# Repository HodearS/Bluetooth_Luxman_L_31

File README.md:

### 🇫🇷 Version Française
                    
# Luxman L-31 - Module Bluetooth & DAC Interne

Ce dépôt contient les fichiers de conception matérielle d'une carte d'extension Bluetooth conçue spécifiquement pour s'intégrer à l'intérieur d'un amplificateur intégré Luxman L-31.

L'objectif est d'ajouter une connectivité sans fil moderne (aptX-HD) sans dénaturer l'esthétique d'origine de l'appareil ni altérer la qualité de son chemin analogique.

## Architecture technique

La carte s'alimente directement sur le rail de puissance interne de l'amplificateur (environ 40V DC). Le basculement du signal audio est géré par un relais de signal pour garantir que les entrées analogiques d'origine restent totalement isolées lorsque le module est inactif.

Points clés de la conception :
* **Alimentation :** Utilisation d'un régulateur abaisseur (Buck) acceptant jusqu'à 65V en entrée pour tolérer les variations du rail d'alimentation du Luxman.
* **CEM et Bruit :** Le convertisseur Buck fonctionne en mode "Forced PWM" (fréquence fixe de 400 kHz) afin de repousser le bruit de découpage hors de la bande audible. Le routage sur 4 couches inclut des plans de masse dédiés, du via stitching et des zones d'exclusion RF strictes autour de l'antenne.
* **Chemin audio :** Les composants passifs traitant le signal analogique en sortie de DAC utilisent des condensateurs à diélectrique C0G/NP0 et des résistances à couche mince (thin film) pour éviter l'introduction de distorsions harmoniques.

## Spécifications matérielles

* **Logiciel CAO :** KiCad 10
* **PCB :** 4 couches
* **Régulateur 5V :** Texas Instruments LMR51606XFDBVR
* **LDO 3.3V :** Texas Instruments TPS7A2033PDBVR (avec décharge active)
* **DAC :** ESS Technology ES9023P
* **Module Bluetooth :** Feasycom FSC-BT1026E (sortie I2S/PCM)
* **Relais Audio :** Omron G6K-2F-Y DC3

## Structure du dépôt

Ce dépôt héberge uniquement les fichiers sources du projet KiCad (`.kicad_pro`, `.kicad_sch`, `.kicad_pcb` et BOM). Les fichiers de fabrication (Gerbers, fichiers de placement CPL) ne sont pas versionnés.

## Avertissement de sécurité

L'installation de ce module implique d'intervenir à l'intérieur d'un amplificateur relié au secteur et de manipuler des tensions continues de puissance. Ces modifications s'adressent à des personnes ayant les compétences requises en électronique. Toute modification est effectuée à vos propres risques.

### 🇬🇧 English Version

# Luxman L-31 - Internal Bluetooth & DAC Module

This repository contains the hardware design files for a Bluetooth extension board specifically designed to be integrated inside a Luxman L-31 integrated amplifier.

The goal is to add modern wireless connectivity (aptX-HD) without altering the original aesthetics of the device or degrading its analog signal path.

## Technical Architecture

The board is powered directly from the amplifier's internal power rail (approx. 40V DC). Audio signal switching is handled by a signal relay to ensure the original analog inputs remain completely isolated when the module is inactive.

Key design points:
* **Power Supply:** Use of a step-down (Buck) regulator accepting up to 65V input to tolerate fluctuations in the Luxman's power rail.
* **EMC and Noise:** The Buck converter operates in "Forced PWM" mode (fixed 400 kHz frequency) to push switching noise out of the audible band. The 4-layer routing includes dedicated ground planes, via stitching, and strict RF keep-out zones around the antenna.
* **Audio Path:** Passive components handling the analog signal at the DAC output use C0G/NP0 dielectric capacitors and thin film resistors to prevent the introduction of harmonic distortion.

## Hardware Specifications

* **CAD Software:** KiCad 10
* **PCB:** 4 layers
* **5V Regulator:** Texas Instruments LMR51606XFDBVR
* **3.3V LDO:** Texas Instruments TPS7A2033PDBVR (with active discharge)
* **DAC:** ESS Technology ES9023P
* **Bluetooth Module:** Feasycom FSC-BT1026E (I2S/PCM output)
* **Audio Relay:** Omron G6K-2F-Y DC3

## Repository Structure

This repository hosts only the KiCad project source files (`.kicad_pro`, `.kicad_sch`, `.kicad_pcb` and BOM). Manufacturing files (Gerbers, CPL placement files) are not versioned.

## Safety Warning

Installing this module involves working inside a mains-connected amplifier and handling high-power DC voltages. These modifications are intended for individuals with the required electronics skills. All modifications are performed at your own risk.

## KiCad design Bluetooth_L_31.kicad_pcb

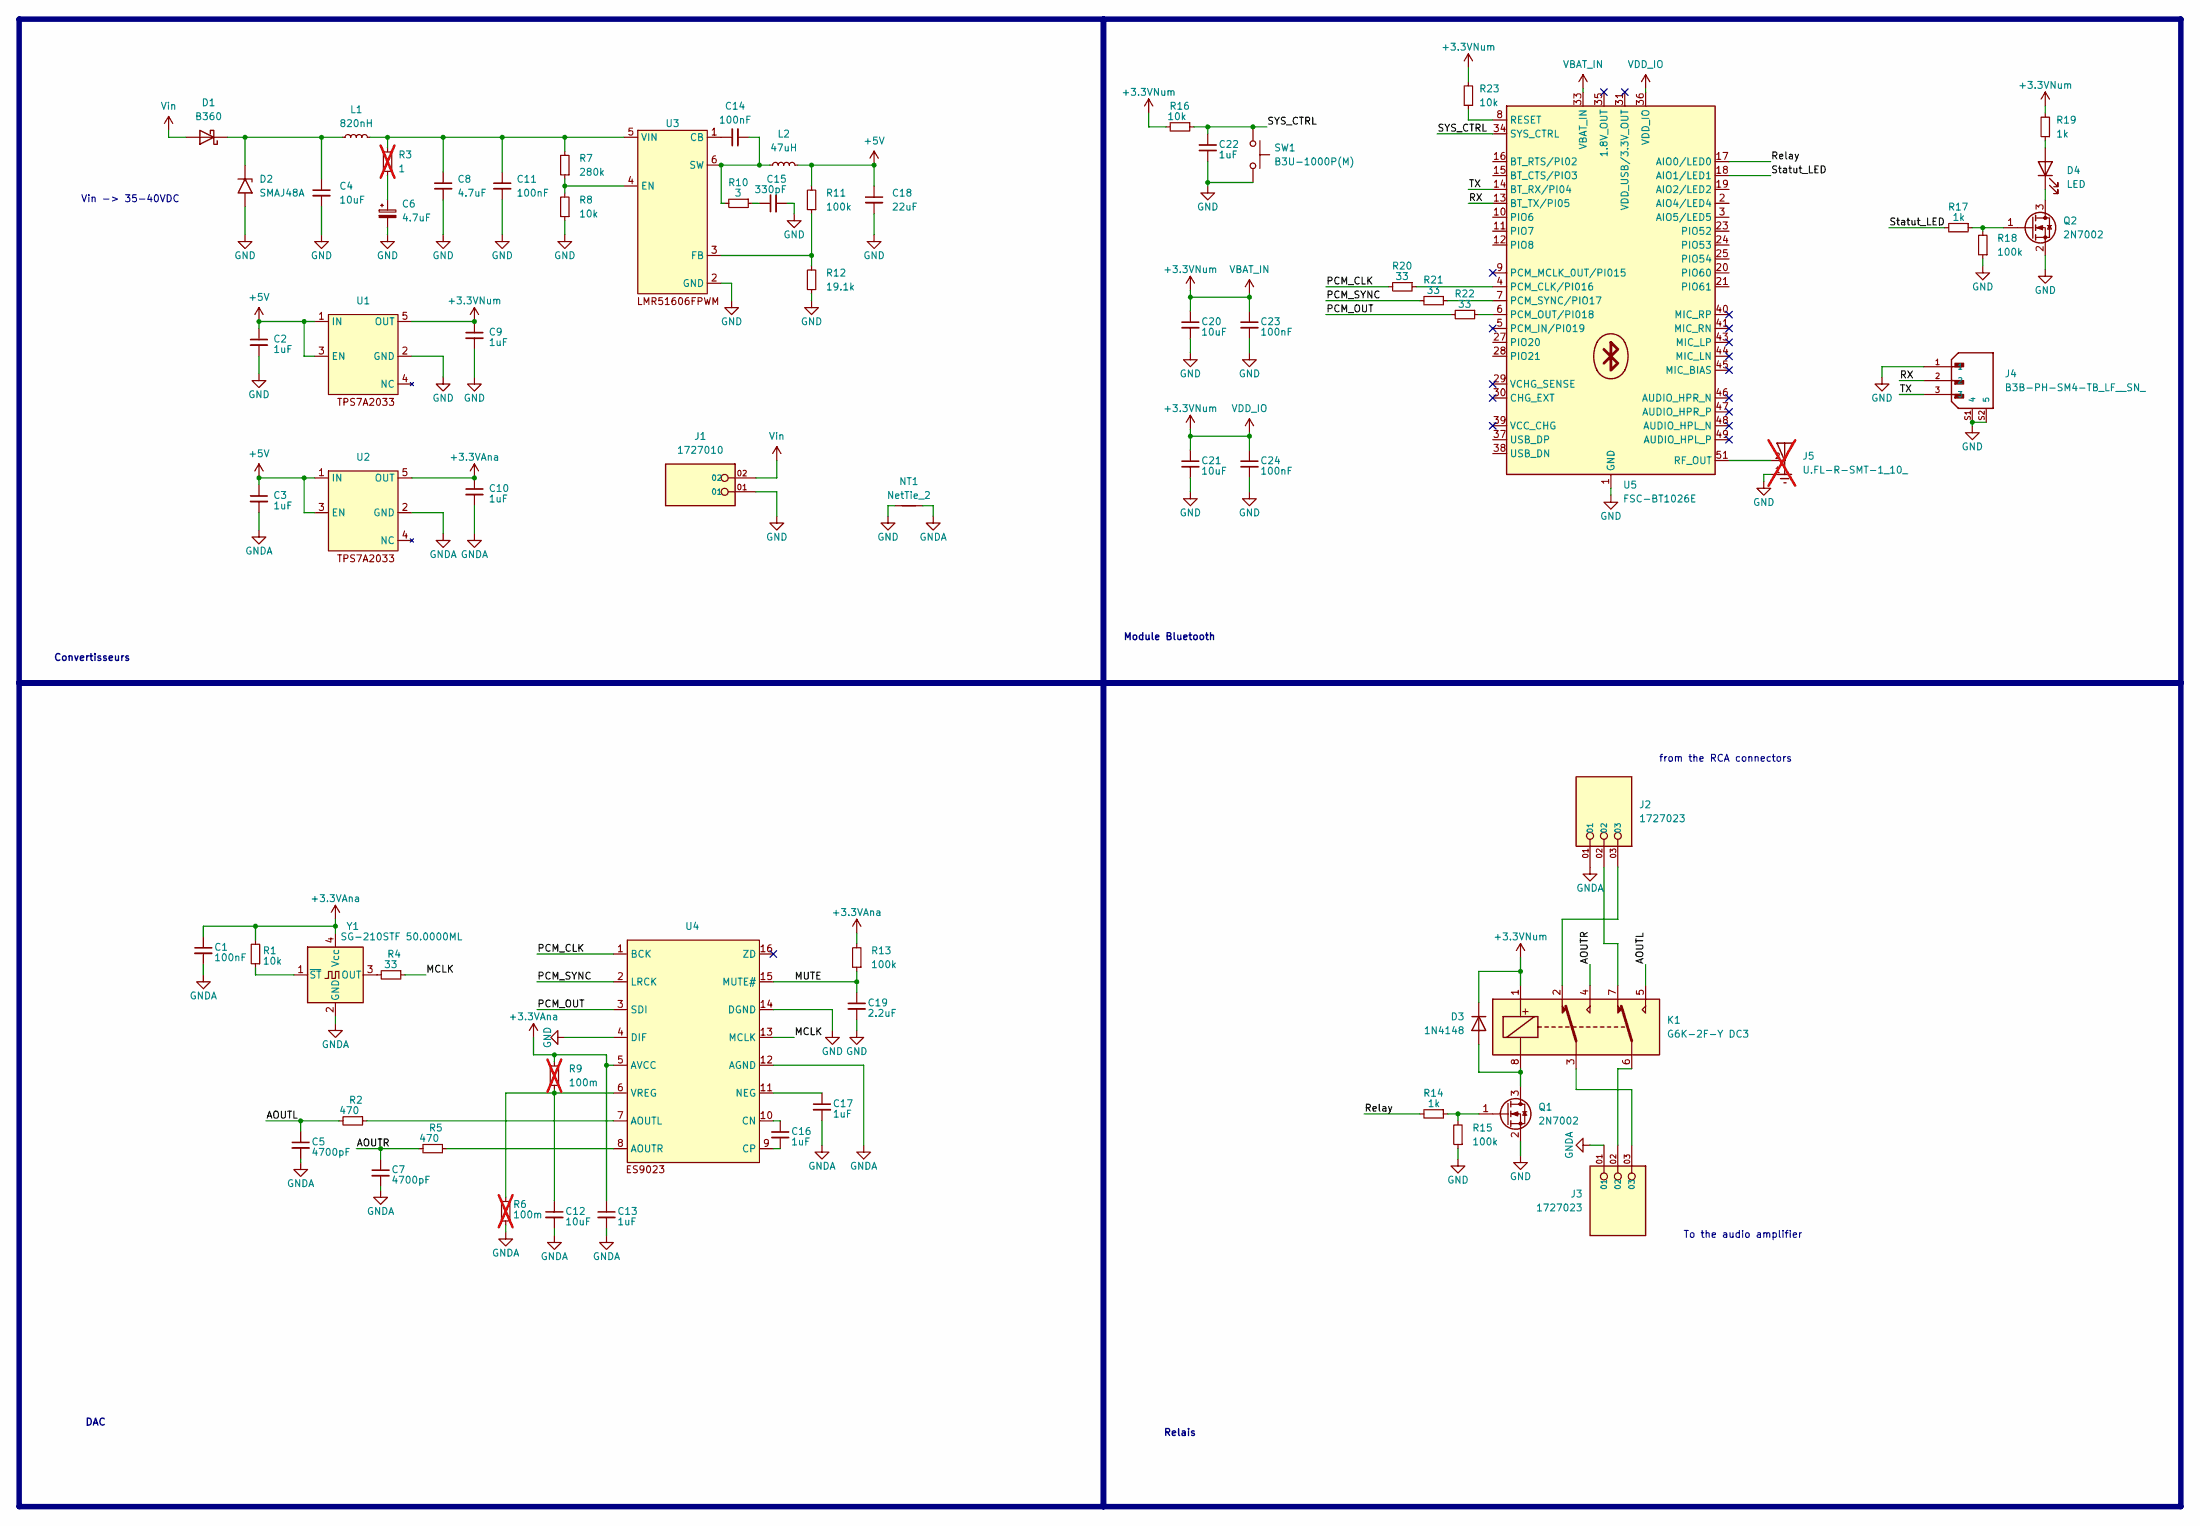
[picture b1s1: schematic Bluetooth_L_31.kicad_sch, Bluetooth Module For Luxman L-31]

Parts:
C1, C11, C14, C23, C24: 100nF; C_0805_2012Metric
C2, C3, C9, C10, C13, C16, C17, C22: 1uF; C_0805_2012Metric
C4: 10uF; C_1210_3225Metric
C5, C7: 4700pF; C_0805_2012Metric
C6, C8: 4.7uF; C_1210_3225Metric
C12, C20, C21: 10uF; C_0805_2012Metric
C15: 330pF; C_0805_2012Metric
C18: 22uF; C_1210_3225Metric
C19: 2.2uF; C_0805_2012Metric
D1: B360; D_SMC
D2: SMAJ48A; D_SMA
D3: 1N4148; D_SOD-123
D4: LED; LED_0805_2012Metric
J1: 1727010; PHOENIX_1727010; PARTREV 03.03.2021
J2, J3: 1727023; PHOENIX_1727023; PARTREV 03.03.2021
J4: B3B-PH-SM4-TB_LF__SN_; JST_B3B-PH-SM4-TB_LF__SN_; PARTREV N/A
J5: U.FL-R-SMT-1_10_; HRS_U.FL-R-SMT-1_10_; not fitted
K1: G6K-2F-Y DC3; Relay_DPDT_Omron_G6K-2F-Y
L1: 820nH; L_1210_3225Metric
L2: 47uH; L_Bourns-SRN4018
NT1: NetTie_2; NetTie-2_SMD_Pad2.0mm
Q1, Q2: 2N7002; SOT-23-3
R1, R8, R16, R23: 10k; R_0805_2012Metric
R2, R5: 470; R_0805_2012Metric
R3: 1; R_0805_2012Metric; not fitted
R4, R20, R21, R22: 33; R_0805_2012Metric
R6, R9: 100m; R_0805_2012Metric; not fitted
R7: 280k; R_0805_2012Metric
R10: 3; R_0805_2012Metric
R11, R13, R15, R18: 100k; R_0805_2012Metric
R12: 19.1k; R_0805_2012Metric
R14, R17, R19: 1k; R_0805_2012Metric
SW1: B3U-1000P(M); SW_B3U-1000PM
U1, U2: SOT-23-5
U3: LMR51606FPWM; SOT-23-6
U4: SOP-16_4.4x10.4mm_P1.27mm
U5: FSC-BT1026E; FSC-BT1026x
Y1: SG-210STF 50.0000ML; Oscillator_SMD_SeikoEpson_SG210-4Pin_2.5x2.0mm

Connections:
+3.3VAna: C1.1, C10.1, C13.1, R1.2, R9.2, R13.2, U2.5 (OUT), U4.5 (AVCC), Y1.4 (Vcc)
+3.3VNum: C9.1, C20.1, C21.1, C23.1, C24.1, D3.1 (K), K1.1, R16.2, R19.2, R23.2, U1.5 (OUT), U5.33 (VBAT_IN), U5.36 (VDD_IO)
+5V: C2.1, C3.1, C18.1, L2.2, R11.2, U1.1 (IN), U1.3 (EN), U2.1 (IN), U2.3 (EN)
/AOUTL: C5.1, K1.5, R2.2
/AOUTR: C7.1, K1.4, R5.2
/MCLK: R4.1, U4.13 (MCLK)
/MUTE: C19.1, R13.1, U4.15 (MUTE#)
/PCM_CLK: R20.2, U4.1 (BCK)
/PCM_OUT: R22.2, U4.3 (SDI)
/PCM_SYNC: R21.2, U4.2 (LRCK)
/RX: J4.2, U5.13 (BT_TX/PI05)
/Relay: R14.2, U5.17 (AIO0/LED0)
/SYS_CTRL: C22.1, R16.1, SW1.1, U5.34 (SYS_CTRL)
/Statut_LED: R17.2, U5.18 (AIO1/LED1)
/TX: J4.3, U5.14 (BT_RX/PI04)
GND: C2.2, C4.2, C6.2, C8.2, C9.2, C11.2, C15.2, C18.2, C19.2, C20.2, C21.2, C22.2, C23.2, C24.2, D2.2 (A2), J1.01, J4.1, J4.S1 (4), J4.S2 (5), J5.1, J5.3, NT1.1, Q1.2 (S), Q2.2 (S), R8.1, R12.1, R15.1, R18.1, SW1.2, U1.2 (GND), U3.2 (GND), U4.4 (DIF), U4.14 (DGND), U5.1 (GND), U5.22 (GND), U5.32 (GND), U5.50 (GND), U5.52 (GND)
GNDA: C1.2, C3.2, C5.2, C7.2, C10.2, C12.2, C13.2, C17.2, J2.01, J3.01, NT1.2, R6.1, U2.2 (GND), U4.12 (AGND), Y1.2 (GND)
unnamed: C6.1, R3.1
unnamed: C15.1, R10.1
unnamed: C4.1, D1.1 (K), D2.1 (A1), L1.1
unnamed: D3.2 (A), K1.8, Q1.3 (D)
unnamed: D4.2 (A), R19.1
unnamed: D4.1 (K), Q2.3 (D)
unnamed: J2.02, K1.7
unnamed: J2.03, K1.2
unnamed: J3.02, K1.6
unnamed: J3.03, K1.3
unnamed: Q1.1 (G), R14.1, R15.2
unnamed: Q2.1 (G), R17.1, R18.2
unnamed: C14.1, U3.1 (CB)
unnamed: R7.1, R8.2, U3.4 (EN)
unnamed: R11.1, R12.2, U3.3 (FB)
unnamed: C14.2, L2.1, R10.2, U3.6 (SW)
unnamed: C8.1, C11.1, L1.2, R3.2, R7.2, U3.5 (VIN)
unnamed: R2.1, U4.7 (AOUTL)
unnamed: R5.1, U4.8 (AOUTR)
unnamed: C16.1, U4.10 (CN)
unnamed: C16.2, U4.9 (CP)
unnamed: C17.1, U4.11 (NEG)
unnamed: C12.1, R6.2, R9.1, U4.6 (VREG)
unnamed: R20.1, U5.4 (PCM_CLK/PI016)
unnamed: R22.1, U5.6 (PCM_OUT/PI018)
unnamed: R21.1, U5.7 (PCM_SYNC/PIO17)
unnamed: R23.1, U5.8 (RESET)
unnamed: J5.2, U5.51 (RF_OUT)
unnamed: R4.2, Y1.3 (OUT)
unnamed: R1.1, Y1.1 (~ST)
Vin: D1.2 (A), J1.02

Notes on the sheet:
from the RCA connectors
DAC
Module Bluetooth
Vin -> 35-40VDC
Convertisseurs
To the audio amplifier
Relais

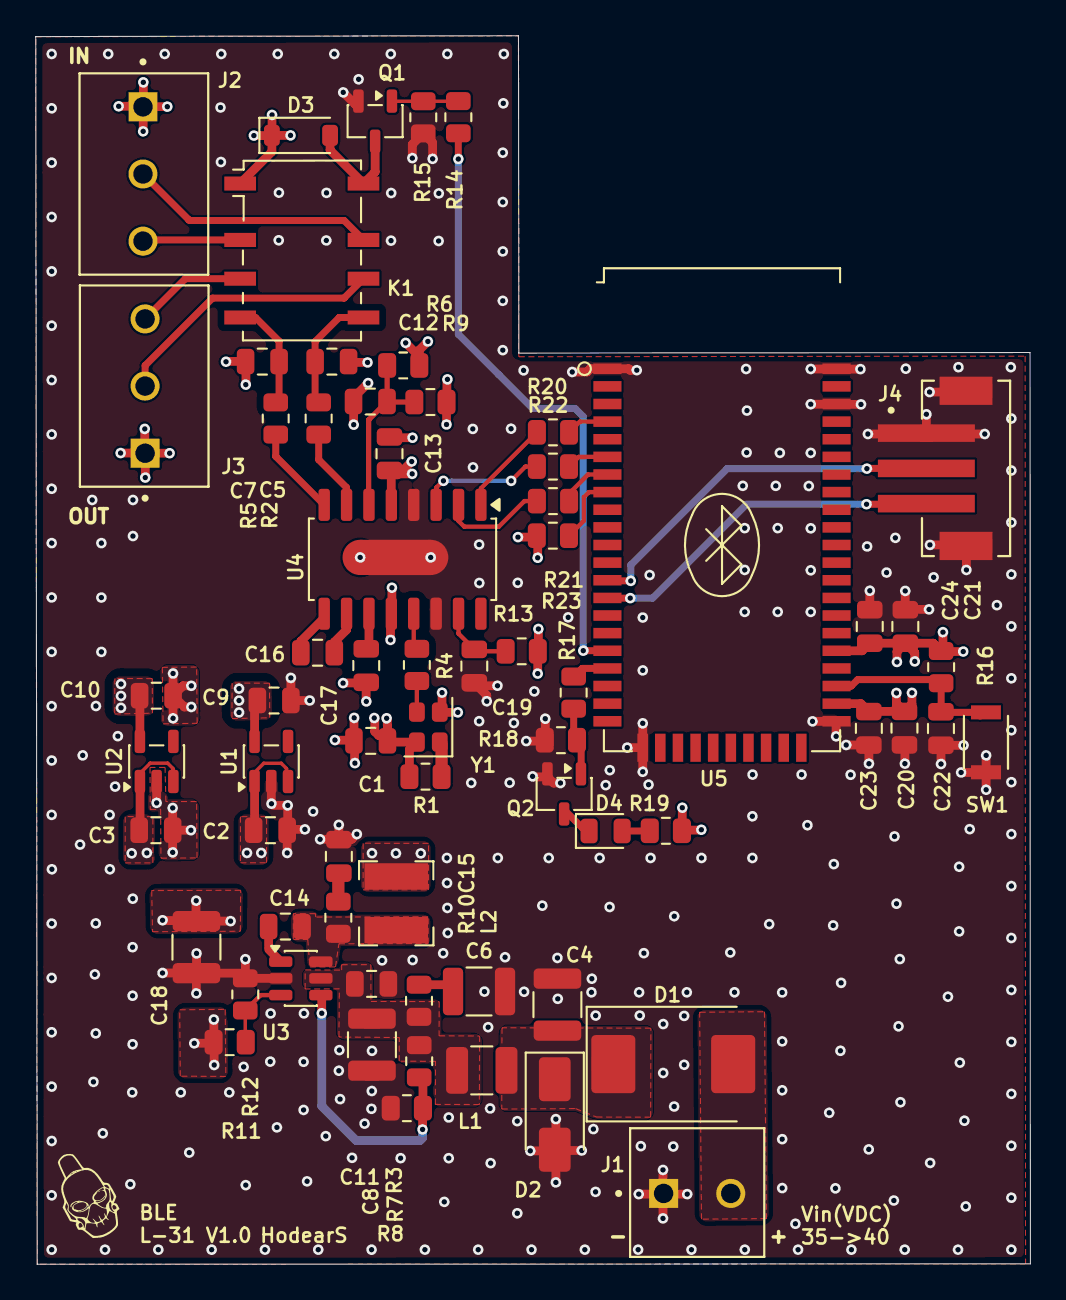
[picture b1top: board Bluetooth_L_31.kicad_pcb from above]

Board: 4 copper layers, 56.4 x 69.7 mm, 68 parts (0 on the bottom side), 47 nets.

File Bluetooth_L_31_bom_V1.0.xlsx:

Component | References | Description | Value | Footprint | Quantity Per PCB | Prix/unité | Total | Quantité/commande | Total/commande
1 | C15 | GRM2165C2A331JA01D | 330pF | C_0805_2012Metric | 1 | 7.3999999999999996E-2 | 7.3999999999999996E-2 | 10 | 0.74
2 | C5 C7 | 08051A472KAT2A | 4700pF | C_0805_2012Metric | 2 | 0.29499999999999998 | 0.59 | 10 | 2.9499999999999997
3 | C1 C11 C14 C23 C24 | CL21B104KCFSFNE | 100nF | C_0805_2012Metric | 5 | 2.7E-2 | 0.13500000000000001 | 20 | 0.54
4 | C2 C3 C9 C10 C13 C16 C17 C22 | CL21B105KBFNNNF | 1uF | C_0805_2012Metric | 8 | 3.7999999999999999E-2 | 0.30399999999999999 | 20 | 0.76
5 | C19 | CL21B225KAFNNNF | 2.2uF | C_0805_2012Metric | 1 | 4.1000000000000002E-2 | 4.1000000000000002E-2 | 10 | 0.41000000000000003
6 | C6 C8 | GRM32DL8EL475KE07L | 4.7uF | C_1210_3225Metric | 2 | 3.61E-2 | 7.22E-2 | 10 | 0.36099999999999999
7 | C12 C20 C21 | GRM21BZ71E106KE15K | 10uF | C_0805_2012Metric | 3 | 0.11899999999999999 | 0.35699999999999998 | 10 | 1.19
8 | C4 | CL32B106KMVNNWE | 10uF | C_1210_3225Metric | 1 | 0.38 | 0.38 | 10 | 3.8
9 | C18 | CL32B226KAJNNNE | 22uF | C_1210_3225Metric | 1 | 0.23799999999999999 | 0.23799999999999999 | 10 | 2.38
10 | D3 | 100V 0.15A standard switching diode, DO-35 | 1N4148 | D_SOD-123 | 1 | 8.6999999999999994E-2 | 8.6999999999999994E-2 | 10 | 0.86999999999999988
11 | D1 | B360-13-F | B360 | D_SMC | 1 | 0.35 | 0.35 | 10 | 3.5
12 | D4 | 150080GS75000 | LED | LED_0805_2012Metric | 1 | 0.161 | 0.161 | 10 | 1.61
13 | D2 | SMAJ48A | SMAJ48A | D_SMA | 1 | 0.27500000000000002 | 0.27500000000000002 | 10 | 2.75
14 | J1 | 1727010 | 1727010 | PHOENIX_1727010 | 1 | 0.97199999999999998 | 0.97199999999999998 | 2 | 1.944
15 | J2 J3 | 1727023 | 1727023 | PHOENIX_1727023 | 2 | 1.45 | 2.9 | 4 | 5.8
16 | J4 | B3B-PH-SM4-TB(LF)(SN) | B3B-PH-SM4-TB_LF__SN_ | JST_B3B-PH-SM4-TB_LF__SN_ | 1 | 0.38700000000000001 | 0.38700000000000001 | 2 | 0.77400000000000002
17 | K1 | G6K-2F-Y-DC3 | G6K-2F-Y DC3 | Relay_DPDT_Omron_G6K-2F-Y | 1 | 3.15 | 3.15 | 2 | 6.3
18 | L1 | LQH32PN1R0NN0L | 820nH | L_1210_3225Metric | 1 | 0.188 | 0.188 | 10 | 1.88
19 | L2 | SRN4018-470M | 47uH | L_Bourns-SRN4018 | 1 | 0.26400000000000001 | 0.26400000000000001 | 10 | 2.64
20 | Q1 Q2 | 2N7002LT1G | 2N7002 | SOT-23-3 | 2 | 0.16400000000000001 | 0.32800000000000001 | 10 | 1.6400000000000001
21 | R6 R9 | Resistor, small symbol | 100m | R_0805_2012Metric | 2 (DNF) |  |  |  | 0
22 | R3 | Resistor, small symbol | 1 | R_0805_2012Metric | 1 (DNF) |  |  |  | 0
23 | R10 | RC0805FR-073RL | 3 | R_0805_2012Metric | 1 | 2.4E-2 | 2.4E-2 | 10 | 0.24
24 | R4 R20 R21 R22 | RC0805FR-0733RL | 33 | R_0805_2012Metric | 4 | 1.4999999999999999E-2 | 0.06 | 10 | 0.15
25 | R2 R5 | ERA-6AEB471V | 470 | R_0805_2012Metric | 2 | 6.4000000000000001E-2 | 0.128 | 10 | 0.64
26 | R14 R17 R19 | RC0805FR-071KL | 1k | R_0805_2012Metric | 3 | 1.7999999999999999E-2 | 5.3999999999999992E-2 | 10 | 0.18
27 | R1 R8 R16 R23 | RC0805FR-0710KL | 10k | R_0805_2012Metric | 4 | 1.7999999999999999E-2 | 7.1999999999999995E-2 | 10 | 0.18
28 | R12 | RC0805FR-0719K1L | 19.1k | R_0805_2012Metric | 1 | 1.7000000000000001E-2 | 1.7000000000000001E-2 | 10 | 0.17
29 | R11 R13 R15 R18 | RC0805FR-07100KL | 100k | R_0805_2012Metric | 4 | 1.7999999999999999E-2 | 7.1999999999999995E-2 | 10 | 0.18
30 | R7 | RC0805FR-07280KL | 280k | R_0805_2012Metric | 1 | 1.4999999999999999E-2 | 1.4999999999999999E-2 | 10 | 0.15
31 | SW1 | B3U-1000PM | B3U-1000P(M) | SW_B3U-1000PM | 1 | 1.08 | 1.08 | 1 | 1.08
32 | U5 | FSC-BT1026E | FSC-BT1026E | FSC-BT1026x | 1 | 8 | 8 | 1 | 8
33 | U3 | LMR51606XFQDBVRQ1 | LMR51606FPWM | SOT-23-6 | 1 | 1.4 | 1.4 | 1 | 1.4
34 | U1 U2 | TPS7A2033PDBVR | ~ | SOT-23-5 | 2 | 0.224 | 0.44800000000000001 | 5 | 1.1200000000000001
35 | U4 | ES9023P | ~ | SOP-16_4.4x10.4mm_P1.27mm | 1 | 1.19 | 1.19 | 4 | 4.76
36 | Y1 | SG-210STF 50.0000ML | SG-210STF 50.0000ML | Oscillator_SMD_SeikoEpson_SG210-4Pin_2.5x2.0mm | 1 | 2.12 | 2.12 | 1 | 2.12
 |  |  |  |  |  | Coût total/cartes | 25.933199999999999 | 283 | 63.208999999999989
Component Groups: | 36
Component Count: | 67
Fitted Components: | 64
Number of PCBs: | 1
Total components: | 64
Schematic Version: | V1.0
Schematic Date: | 2026-06-17
BoM Date: | 2026-06-19T23:25:48
Schematic Source: | Bluetooth_L_31.kicad_sch
KiCad Version: | Eeschema 10.0.3

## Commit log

2026-06-19 Initialisation : Routage complet du module Bluetooth pour le Luxman L-31
2026-06-19 Create README.md
    description du projet
